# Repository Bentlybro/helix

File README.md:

# Helix

A modular behind-the-ear wearable platform. The ear clip is the mount — snap any module onto it magnetically.

## Concept

Helix is not a single-purpose device. It's a **platform**.

The ear clip attaches to your ear and stays there. Different electronic modules magnetically connect to it — each with their own MCU, sensors, and purpose. Swap modules, change what the device does. The clip is the constant, the module is the variable.

Current modules:
- **Helix IMU** — head pose tracking (roll, pitch, yaw) over BLE
- **Helix Mic** — microphone audio streaming over BLE for speech-to-text

Planned modules: anything that fits behind an ear.

## Hardware

### Ear Clip
3D printed, behind-the-ear hook design with magnetic mounting face. Sits discreetly over the ear like a hearing aid. Houses no electronics — purely mechanical.

### Helix IMU Module
- **MCU**: Seeed XIAO nRF52840 Sense
- **IMU**: Onboard LSM6DS3 (accel + gyro) — 6DOF, 200Hz
- **Connectivity**: BLE 5.0
- **Power**: LP502030 250mAh LiPo + slide switch
- **Extras**: Battery % monitoring, onboard temperature sensor

### Helix Mic Module
- **MCU**: Seeed XIAO nRF52840 Sense
- **Mic**: Onboard PDM microphone — 16kHz 16-bit mono
- **Connectivity**: BLE 5.0
- **Firmware**: Zephyr RTOS

## Repository Structure

```
helix/
├── firmware/
│   ├── helix-imu/          # Arduino (Seeed nRF52 Boards)
│   │   └── helix-imu.ino
│   └── helix-mic/          # Zephyr RTOS (nRF Connect SDK v2.5.0)
│       ├── CMakeLists.txt
│       ├── prj.conf
│       ├── boards/
│       └── src/
├── apps/
│   ├── helix-imu/              # Python BLE receiver (testing)
│   │   ├── receiver.py
│   │   └── scan.py
│   ├── helix-imu-android/      # Android app — live orientation + visualiser
│   └── helix-mic-android/      # Android app — audio stream + Whisper STT
└── hardware/                   # 3D models (coming soon)
```

## BLE Protocol

All Helix modules share a common service UUID with module-specific characteristics.

**Service UUID:** `917649A0-D98E-11E5-9EEC-0002A5D5C51B`

| Characteristic | UUID | Module | Format |
|---|---|---|---|
| Orientation | `917649A1-...` | IMU | 3x float32 (roll, pitch, yaw °) |
| Battery | `917649A2-...` | IMU, Mic | uint8 (0–100%) |
| Temperature | `917649A3-...` | IMU | float32 (°C) |
| Audio | `917649B0-...` | Mic | [seq:2][flags:1][pcm data] |

## Getting Started

### Helix IMU

**Flash firmware (Arduino):**
1. Install Arduino IDE
2. Add board URL: `https://files.seeedstudio.com/arduino/package_seeeduino_arduino_board_index.json`
3. Install **Seeed nRF52 Boards** (non-mbed variant)
4. Install **Seeed Arduino LSM6DS3** library
5. Select **Seeed XIAO BLE Sense - nRF52840**
6. Open `firmware/helix-imu/helix-imu.ino` and upload

**Android app:**
Open `apps/helix-imu-android/` in Android Studio and run.

Features: live roll/pitch/yaw display, 3D direction visualiser, calibration, battery %, temperature.

### Helix Mic

**Flash firmware (Zephyr):**
1. Build with nRF Connect SDK v2.5.0
2. Double-tap reset on XIAO to enter bootloader
3. Drag `zephyr.uf2` onto the `XIAO-SENSE` drive

**Android app:**
Open `apps/helix-mic-android/` in Android Studio and run.

Features: BLE audio receive, WAV buffering, Whisper API transcription.

## Building Firmware (Server)

nRF Connect SDK is set up on the build server.

```bash
# Helix Mic (Zephyr)
cd ~/nrf-sdk/zephyr
west build -b xiao_ble ~/clawd/repos/helix/firmware/helix-mic

# Output
build/zephyr/zephyr.uf2
```

## Status

| Module | Firmware | Android App | Hardware |
|---|---|---|---|
| Helix IMU | ✅ Working | ✅ Working | 🚧 Enclosure in progress |
| Helix Mic | ✅ Advertising | 🚧 In progress | ⬜ Not started |

## License

MIT

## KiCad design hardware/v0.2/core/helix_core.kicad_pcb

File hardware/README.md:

# Helix hardware

Helix as a product: a small computer worn behind the ear, and modules that snap onto it.
The boards here are designed as code with [Via](https://github.com/ThyFriendlyFox/via): each board is
a `design.py`, and the KiCad files, the gerbers and the pictures are generated from it.

## Current version: v0.2

Helix is 2 pieces: a plain printed **hook**, and one **pod** that holds everything and snaps onto
the hook's spine with 3 magnets (6 x 2 mm, 10.4 mm apart). Hooks come in sizes; the pod stays the
same. A different kind of Helix is a different pod on the same hook.

[`v0.2/core`](v0.2/core/design.py) is the pod's board, 13 x 46 mm. Against v0.1 it adds a USB-C socket
to charge and flash, a side-push button on the pod's rear edge, and 2 pads for a wireless charging
receiver; v0.1's module port and its Health board are dropped, and no health sensor is fitted (hair
lies between the pod and the skin). The cell is an LP401230 with its protection circuit, 100 mAh,
over the whole top face. The board is held to PCBWay's published limits. Its gates: ERC, DRC, SIM
and EXPORT pass, GREEN with 2 warnings (the socket's outline drawing runs over the board's edge).
Nobody has built it. [`v0.2/order`](v0.2/order/make_order.py) writes the 3 files PCBWay's order
form takes; its part numbers have not been checked against stock.

Everything below this section describes v0.1 and is kept as its record.

## The product (v0.1)

| Piece | What it is | Electronics |
|---|---|---|
| **Clip** | The hook over the ear. Printed or moulded, in sizes. Magnets hold the Core to it. | None |
| **Core** | The body behind the ear: radio, motion, microphone, cell, charger, one button, one light. Useful on its own. | [`v0.1/core`](v0.1/core/design.py) |
| **Module** | A small board that snaps onto the Core's Helix Port and adds a sense or an output. | [`v0.1/health`](v0.1/health/design.py) is the first |
| **Dock** | Where the Core sits to charge. It meets the same port, so it can also flash firmware over USB. | Not designed yet |

The first prototypes were a Seeed XIAO nRF52840 Sense and a 250 mAh cell in a printed box of
27 x 40 x 13 mm (`3D models/`). The Core's board is 13 x 38 mm. With a cell of about 100 mAh on top and
1 mm of shell, the body comes to about 15 x 40 x 9 mm: half the width and a third of the volume.

## The Helix Port

10 contacts on a 2 x 5 grid, 2.54 mm apart. The Core carries flat gold pads on its back face; a
module or the dock carries spring pins. 2 magnets in each shell, poles opposed, hold the pair and
let it seat only one way round. Seen from above the Core's top face:

| 1 VCHG | 3 GND | 5 USB D+ | 7 USB D- | 9 INT |
|---|---|---|---|---|
| **2 3V0** | **4 GND** | **6 SDA** | **8 SCL** | **10 VMOD** |

| Contact | Direction | What |
|---|---|---|
| VCHG | in | 5 V from a dock. Charges the cell and wakes USB. |
| 3V0 | out | The Core's 3.0 V rail: a module's logic reference. |
| VMOD | out | The cell, 3.0 to 4.2 V, through a load switch. Off until the firmware turns it on; soft start, so snapping a module on does not dip the cell. |
| SDA, SCL | both | I2C at 400 kHz, pulled up to 3V0 on the Core. A module adds 25 pF at most. |
| INT | in | Open drain, active low, pulled up on the Core. A module asks for attention. |
| USB D+, D- | both | The nRF52840's own USB, for the dock. |

A module is found by its I2C addresses. v0.2 should add a small ID EEPROM to every module so the
Core can name what is attached without guessing.

## Core v0.1

| | |
|---|---|
|  |  |

13 x 38 mm, 4 layers, 0.8 mm, matte black, parts on both faces.

| Block | Part | Why |
|---|---|---|
| Radio and processor | Raytac MDBT50Q-1MV2 (nRF52840, chip antenna) | The chip the XIAO carries, so the Zephyr and Arduino firmware carries over. A certified module: no antenna to design. |
| Motion | ST LSM6DS3TR-C at 0x6A | The XIAO Sense's IMU, on the same address. |
| Microphone | Knowles SPH0641LU4H-1, PDM | On the back face; its sound port is a hole through the board. |
| Charger | Microchip MCP73831, 50 mA | Half-hour rate for a 100 mAh cell. STAT goes to the processor. |
| Rail | TI TLV75530, 3.0 V | Holds regulation until the cell is nearly empty. |
| Module power | TI TPS22917 load switch | VMOD on request, slew-limited, discharged when off. |
| Protection | 3 x TI TPD1E05U06 | A TVS diode on each line the dock drives. |
| Cell voltage | 1M / 1M divider into AIN2 | 2 uA. |
| Wearer | Omron B3U button, a white light | One of each. |
| Debug | 3 pads: SWDIO, SWDCLK, nRESET | With 3V0 and GND from the port. |

Firmware pin map (nRF52840):

| Signal | Pin | Signal | Pin |
|---|---|---|---|
| SDA | P0.26 | SCL | P0.27 |
| PDM clock | P0.06 | PDM data | P0.08 |
| IMU INT1 | P0.05 | Module INT | P0.07 |
| Cell voltage / 2 | P0.04 (AIN2) | Module power enable | P1.08 |
| Charger STAT | P1.09 | Button | P0.11 |
| Light (low is on) | P0.12 | nRESET | P0.18 |

## Health v0.1

| | |
|---|---|
|  |  |

13 x 16 mm, 4 layers, 0.8 mm. Spring pins and a 1.8 V regulator on the face that meets the Core; on
the face against the skin, a MAX30102 (pulse and blood oxygen, 0x57) and a TMP117 (skin
temperature, 0x48). It runs only from VMOD, so it draws nothing until the firmware turns it on.

## Where each board stands

| Board | ERC | DRC | SIM | EXPORT | Verdict |
|---|---|---|---|---|---|
| Core | pass | pass | pass: the I2C rise time, 60 corner runs | pass | GREEN with `--strict` |
| Health | pass | pass | no deck | pass | GREEN with `--strict` |

GREEN means the open tools found no fault in the files. It does not mean a built board works.
Nobody has built either board. Before an order:

- **Parts' ratings are not judged.** Neither board has a `ratings.json`: no pin's voltage, no
  capacitor's derating and no regulator's dissipation has been held to its datasheet by a gate.
- **The antenna is not simulated.** The strip under it is bare on all 4 layers as Raytac asks, but
  the cell lies 0.5 mm from its end and a head is beside it. Range has to be measured.
- **The MAX30102's LED supply** is VMOD, and its datasheet asks 3.1 V at the least: the last part
  of the cell's discharge reads no pulse.
- **The microphone's acoustics** (the hole, the shell's port, a mesh against sweat) are not designed.
- **No cell protection on the board.** The cell must carry its own protection circuit.
- **The I2C bus capacitance** in the deck, 50 pF, is an estimate.
- **The spring pin** is named (Mill-Max 0906 series) and its land is drawn, but its outline has not
  been checked against the drawing, and the stack with the Health module on is about 14 mm thick
  at the port. A lower contact would thin it.
- **Skin contact, sweat and charging while worn** are product-safety questions no gate here asks.

## What comes next

1. The shell and the clip for these boards, sized from the assembly: where the magnets, the button
   cap, the light pipe and the microphone's port go.
2. `ratings.json` for both boards, and the charger and regulator as Via's blocks.
3. The dock: 5 V in on USB-C, 10 spring pins, USB through to the Core.
4. Firmware: one image for the Core with the IMU and microphone services, the new pin map, and
   module detection.
5. v0.2 of the Core: a 32.768 kHz crystal for lower idle current, a module ID EEPROM convention,
   and whatever the first built boards teach.

## Working on the boards

Via runs from its Docker image; nothing else is installed. From `hardware/v0.1`, in Git Bash:

```sh
via() { MSYS_NO_PATHCONV=1 docker run --rm -e KICAD10_3DMODEL_DIR=/bodies \
  -v "$PWD/../.3dmodels:/bodies" -v "$PWD:/work" ghcr.io/thyfriendlyfox/via:main "$@"; }

via python3 footprints/make_footprints.py       # the Helix Port's 2 footprints
via python3 models/make_models.py               # bodies for the parts KiCad draws without one
via workcenter design core/design.py --route    # the Core's KiCad project, routed (about 8 minutes)
via workcenter gates core --strict              # ERC, DRC, simulation, export; GREEN means done
via workcenter pictures .                       # every render into docs/
```

`.3dmodels/` holds the part bodies of KiCad's 3D library that the renders need; it is not in the
repository. The `.kicad_*` files open in KiCad 10 to look at; change `design.py`, never them.
Fabrication files are in `<board>/build/fab/` after the gates.

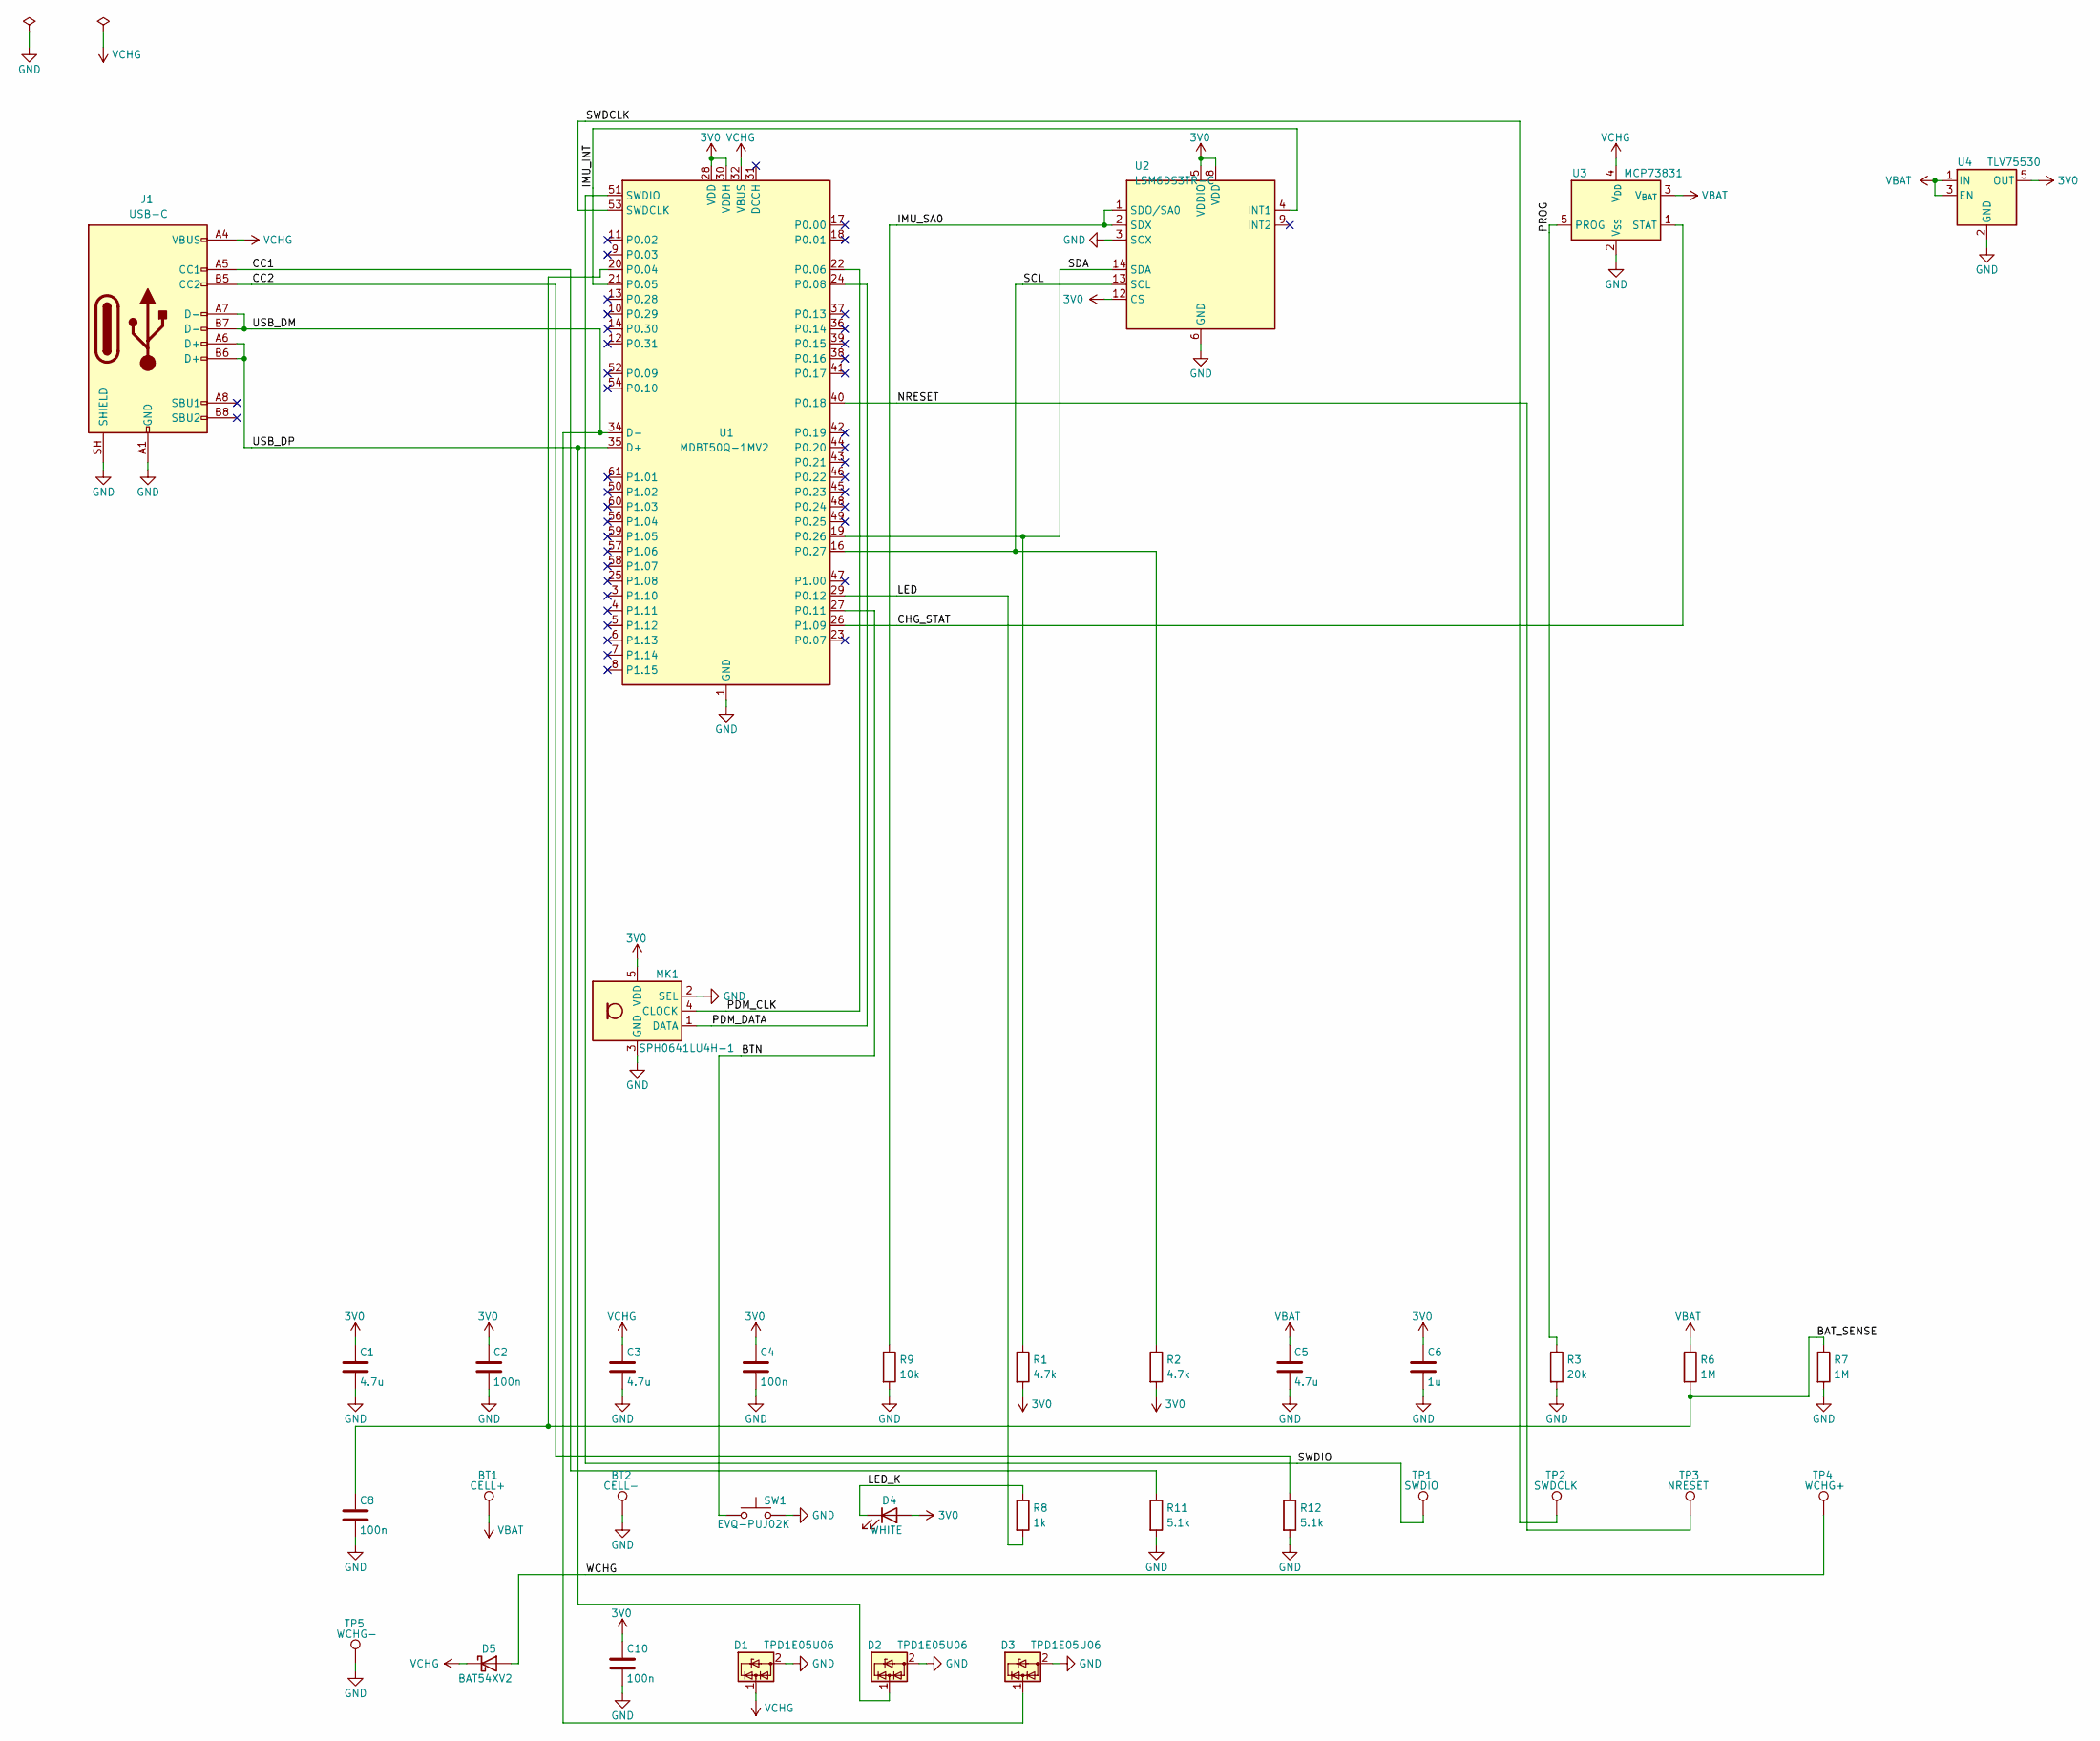
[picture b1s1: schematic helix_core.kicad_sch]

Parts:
BT1: CELL+; TestPoint_Pad_1.5x1.5mm
BT2: CELL-; TestPoint_Pad_1.5x1.5mm
C1, C3, C5: 4.7u; C_0402_1005Metric
C2, C4, C8, C10: 100n; C_0402_1005Metric
C6: 1u; C_0402_1005Metric
D1, D2, D3: TPD1E05U06; D_SOD-523
D4: WHITE; LED_0402_1005Metric
D5: BAT54XV2; D_SOD-523
J1: USB-C; USB_C_Receptacle_HRO_TYPE-C-31-M-12
MK1: SPH0641LU4H-1; Knowles_LGA-5_3.5x2.65mm
R1, R2: 4.7k; R_0402_1005Metric
R3: 20k; R_0402_1005Metric
R6, R7: 1M; R_0402_1005Metric
R8: 1k; R_0402_1005Metric
R9: 10k; R_0402_1005Metric
R11, R12: 5.1k; R_0402_1005Metric
SW1: EVQ-PUJ02K; Panasonic_EVQPUJ_EVQPUA
TP1: SWDIO; TestPoint_Pad_D1.0mm
TP2: SWDCLK; TestPoint_Pad_D1.0mm
TP3: NRESET; TestPoint_Pad_D1.0mm
TP4: WCHG+; TestPoint_Pad_D1.5mm
TP5: WCHG-; TestPoint_Pad_D1.5mm
U1: MDBT50Q-1MV2; Raytac_MDBT50Q
U2: LSM6DS3TR-C; LGA-14_3x2.5mm_P0.5mm_LayoutBorder3x4y
U3: MCP73831; SOT-23-5
U4: TLV75530; SOT-23-5

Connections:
3V0: C1.1, C2.1, C4.1, C6.1, C10.1, D4.2 (A), MK1.5 (VDD), R1.2, R2.2, U1.28 (VDD), U1.30 (VDDH), U2.5 (VDDIO), U2.8 (VDD), U2.12 (CS), U4.5 (OUT)
/BAT_SENSE: C8.1, R6.2, R7.1, U1.20 (P0.04)
/BTN: SW1.1, U1.27 (P0.11)
/CC1: J1.A5 (CC1), R11.1
/CC2: J1.B5 (CC2), R12.1
/CHG_STAT: U1.26 (P1.09), U3.1 (STAT)
/IMU_INT: U1.21 (P0.05), U2.4 (INT1)
/IMU_SA0: R9.1, U2.1 (SDO/SA0), U2.2 (SDX)
/LED: R8.2, U1.29 (P0.12)
/LED_K: D4.1 (K), R8.1
/NRESET: TP3.1, U1.40 (P0.18)
/PDM_CLK: MK1.4 (CLOCK), U1.22 (P0.06)
/PDM_DATA: MK1.1 (DATA), U1.24 (P0.08)
/PROG: R3.1, U3.5 (PROG)
/SCL: R2.1, U1.16 (P0.27), U2.13 (SCL)
/SDA: R1.1, U1.19 (P0.26), U2.14 (SDA)
/SWDCLK: TP2.1, U1.53 (SWDCLK)
/SWDIO: TP1.1, U1.51 (SWDIO)
/USB_DM: D3.1 (I/O), J1.A7 (D-), J1.B7 (D-), U1.34 (D-)
/USB_DP: D2.1 (I/O), J1.A6 (D+), J1.B6 (D+), U1.35 (D+)
/WCHG: D5.2 (A), TP4.1
GND: BT2.1, C1.2, C2.2, C3.2, C4.2, C5.2, C6.2, C8.2, C10.2, D1.2 (GND), D2.2 (GND), D3.2 (GND), J1.A1 (GND), J1.A12 (GND), J1.B1 (GND), J1.B12 (GND), J1.SH (SHIELD), MK1.2 (SEL), MK1.3 (GND), R3.2, R7.2, R9.2, R11.2, R12.2, SW1.2, TP5.1, U1.1 (GND), U1.2 (GND), U1.15 (GND), U1.33 (GND), U1.55 (GND), U2.3 (SCX), U2.6 (GND), U2.7 (GND), U3.2 (V_{SS}), U4.2 (GND)
VBAT: BT1.1, C5.1, R6.1, U3.3 (V_{BAT}), U4.1 (IN), U4.3 (EN)
VCHG: C3.1, D1.1 (I/O), D5.1 (K), J1.A4 (VBUS), J1.A9 (VBUS), J1.B4 (VBUS), J1.B9 (VBUS), U1.32 (VBUS), U3.4 (V_{DD})

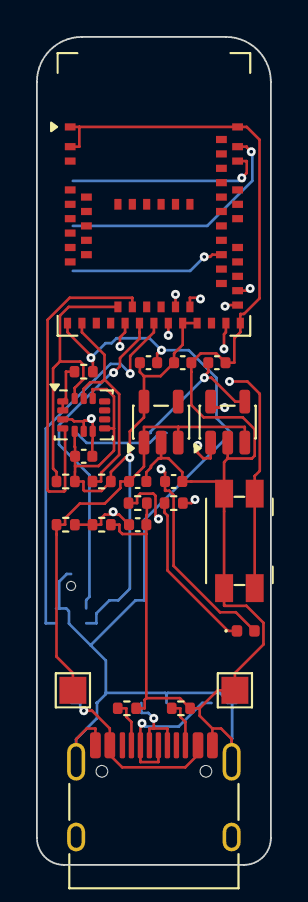
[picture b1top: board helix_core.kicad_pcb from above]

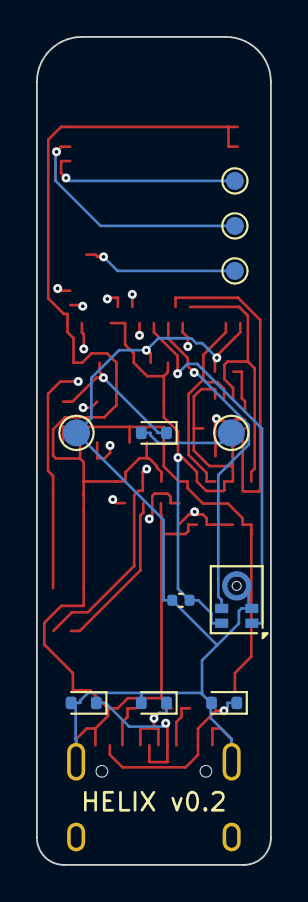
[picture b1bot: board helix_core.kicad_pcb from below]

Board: 4 copper layers, 13.0 x 46.0 mm, 36 parts (11 on the bottom side), 24 nets.

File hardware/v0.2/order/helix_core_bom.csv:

Item,Designator,Qty,Manufacturer,Mfg Part #,Description,Package,Type
1,"C1,C3,C5",3,Murata,GRM155R60J475ME47D,Capacitor 4.7 uF 6.3 V X5R 0402,C_0402_1005Metric,SMD
2,"C2,C4,C8,C10",4,Murata,GRM155R71C104KA88D,Capacitor 100 nF 16 V X7R 0402,C_0402_1005Metric,SMD
3,C6,1,Murata,GRM155R61A105KE15D,Capacitor 1 uF 10 V X5R 0402,C_0402_1005Metric,SMD
4,"D1,D2,D3",3,Texas Instruments,TPD1E05U06DYAR,"TVS diode 5.5 V 0.45 pF, SOD-523",D_SOD-523,SMD
5,D4,1,any,"white LED, 0402, 5 mA",Status light: PCBWay to propose a stocked part,LED_0402_1005Metric,SMD
6,D5,1,onsemi,BAT54XV2T1G,"Schottky diode 30 V 200 mA, SOD-523",D_SOD-523,SMD
7,J1,1,HRO (Korean Hroparts Elec),TYPE-C-31-M-12,"USB Type-C receptacle, 16 pin",USB_C_Receptacle_HRO_TYPE-C-31-M-12,Thru-hole + SMD
8,MK1,1,Knowles,SPH0641LU4H-1,"PDM MEMS microphone, bottom port",Knowles_LGA-5_3.5x2.65mm,SMD
9,"R1,R2",2,Yageo,RC0402FR-074K7L,Resistor 4.7 k 1 % 0402,R_0402_1005Metric,SMD
10,"R11,R12",2,Yageo,RC0402FR-075K1L,Resistor 5.1 k 1 % 0402,R_0402_1005Metric,SMD
11,R3,1,Yageo,RC0402FR-0720KL,Resistor 20 k 1 % 0402,R_0402_1005Metric,SMD
12,"R6,R7",2,Yageo,RC0402FR-071ML,Resistor 1 M 1 % 0402,R_0402_1005Metric,SMD
13,R8,1,Yageo,RC0402FR-071KL,Resistor 1 k 1 % 0402,R_0402_1005Metric,SMD
14,R9,1,Yageo,RC0402FR-0710KL,Resistor 10 k 1 % 0402,R_0402_1005Metric,SMD
15,SW1,1,Panasonic,EVQ-PUJ02K,Side-push tactile switch 4.7 x 3.5 x 1.65 mm,Panasonic_EVQPUJ_EVQPUA,SMD
16,U1,1,Raytac,MDBT50Q-1MV2,"nRF52840 Bluetooth module, chip antenna",Raytac_MDBT50Q,SMD
17,U2,1,STMicroelectronics,LSM6DS3TR-C,"6-axis IMU, LGA-14",LGA-14_3x2.5mm_P0.5mm_LayoutBorder3x4y,SMD
18,U3,1,Microchip,MCP73831T-2ACI/OT,"Li-ion charger 4.2 V, SOT-23-5",SOT-23-5,SMD
19,U4,1,Texas Instruments,TLV75530PDBVR,"Regulator 3.0 V 500 mA, SOT-23-5",SOT-23-5,SMD

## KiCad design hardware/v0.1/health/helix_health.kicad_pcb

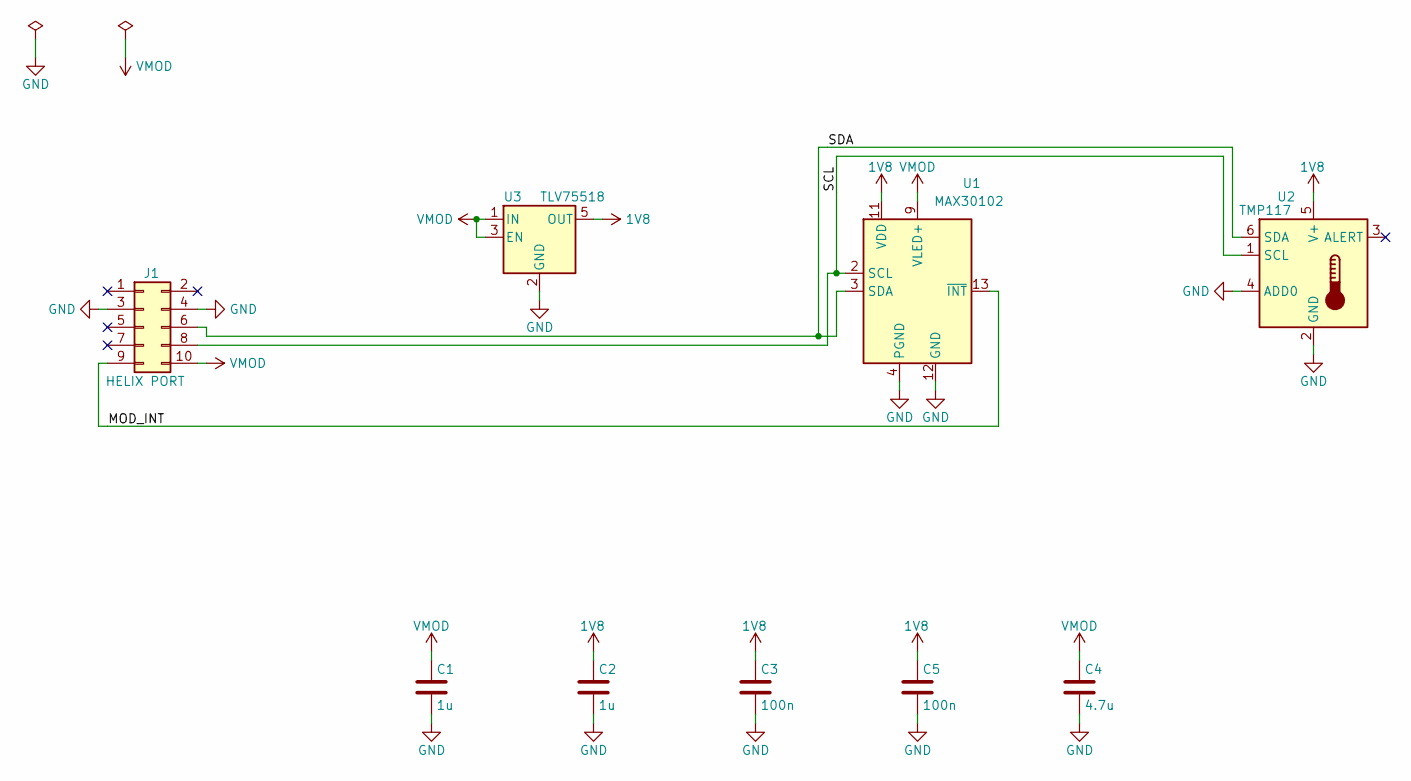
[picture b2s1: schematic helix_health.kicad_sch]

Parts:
C1, C2: 1u; C_0402_1005Metric
C3, C5: 100n; C_0402_1005Metric
C4: 4.7u; C_0402_1005Metric
J1: HELIX PORT; HelixPort_Module_2x05_P2.54mm
U1: MAX30102; Maxim_OLGA-14_3.3x5.6mm_P0.8mm
U2: TMP117; WSON-6-1EP_2x2mm_P0.65mm_EP1x1.6mm
U3: TLV75518; SOT-23-5

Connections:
1V8: C2.1, C3.1, C5.1, U1.11 (VDD), U2.5 (V+), U3.5 (OUT)
/MOD_INT: J1.9, U1.13 (~INT)
/SCL: J1.8, U1.2 (SCL), U2.1 (SCL)
/SDA: J1.6, U1.3 (SDA), U2.6 (SDA)
GND: C1.2, C2.2, C3.2, C4.2, C5.2, J1.3, J1.4, U1.4 (PGND), U1.12 (GND), U2.2 (GND), U2.4 (ADD0), U3.2 (GND)
VMOD: C1.1, C4.1, J1.10, U1.9 (VLED+), U1.10 (VLED+), U3.1 (IN), U3.3 (EN)

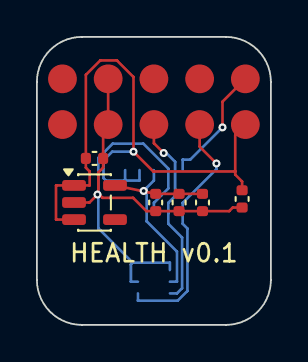
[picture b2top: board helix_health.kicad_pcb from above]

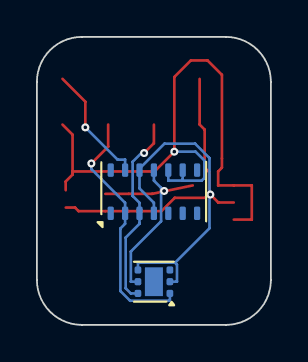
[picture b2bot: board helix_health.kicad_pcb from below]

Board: 4 copper layers, 13.0 x 16.0 mm, 9 parts (2 on the bottom side), 6 nets.

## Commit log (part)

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2026-03-27 Initial idea and planning doc
2026-03-27 Remove Lucid reference — this is its own thing
2026-03-27 Fix firmware for Seeed LSM6DS3 library
    - Use Seeed's LSM6DS3 library (correct for XIAO Sense)
    - Simplify BLE to individual float characteristics
    - Update Python receiver to match
2026-03-27 Fix: use pre-instantiated global IMU object
2026-03-27 Fix: use readAcceleration/readGyroscope API
2026-03-27 Add LED blink status codes + serial wait for debug
2026-03-27 Rewrite BLE using Bluefruit stack (non-mbed board package)
2026-03-27 Fix sensor fusion units: atan2 rad → deg before complementary filter
2026-03-27 Pack orientation into single 12-byte notify, real dt, cleaner receiver
2026-03-27 Move firmware into helix-imu/ folder (Arduino naming requirement)
2026-03-27 Rename receiver-python to helix-imu, add apps README
2026-03-28 Add gradle.properties (useAndroidX, suppressCompileSdk warning)
2026-03-28 Add battery % reading to firmware and Android app
2026-03-28 Add IMU temperature sensor — firmware + Android app
2026-03-28 Fix BLE GATT queue — serialize descriptor writes and reads
2026-03-28 Fix battery: use 3.6V internal ref, remove broken AR_INTERNAL_3_0
2026-03-28 Fix axis: swap pitch/yaw gyro mapping
2026-03-28 Fix axis signs: nod/turn/tilt all positive in correct direction
2026-03-28 Swap forward/up arrows in visualiser
2026-03-28 Fix pitch arrow direction, 200Hz IMU, lower alpha, request high BLE priority
2026-03-28 Swap Forward/Up legend labels in visualiser
2026-03-28 Add navigationBarsPadding so button clears system nav bar
2026-03-28 Add helix-mic Zephyr firmware — PDM mic + BLE audio stream
2026-03-28 Add Helix Mic Android app - BLE audio receiver with Whisper transcription
2026-03-28 Fix transcript card height so connect button is visible
2026-03-28 Fix audio buffer crash — use chunk list instead of ByteArray concat
2026-03-28 fix(helix-mic): buffer size, mic start fallback, PDM device node, connection handling
    - transport.c: increase audio_data buffer from 128 to 700 bytes (20ms PCM at 16kHz = 640 bytes)
    - transport.c: add direct mic start on connect instead of relying on callback
    - main.c: add fallback mic start in main loop if connected but not running
    - main.c: track mic_running state to prevent double starts
    - mic.c: use DT_ALIAS(dmic_dev) with fallback to dmic0/pdm0 node labels
    - xiao_ble.overlay: add dmic-dev alias for broader compatibility
2026-03-28 feat(helix-mic): add USB CDC-ACM serial logging for debug output
    - Enable USB CDC-ACM, UART console, and LOG_BACKEND_UART in prj.conf
    - Call usb_enable() at start of main() with 1s enumeration delay
    - Add detailed error logging around mic start (error code + reason)
    - Add connection/disconnection state logging
    - Firmware now outputs all LOG_INF/WRN/ERR to USB serial at 115200 baud
    View logs: screen /dev/ttyACM0 115200 (Linux/Mac)
2026-03-28 Fix: increase dmic thread stack 1024→4096 bytes (stack overflow crash)
2026-03-28 Fix: write audio CCCD immediately on discover, don't queue it
2026-03-28 Remove USB logging (conflicts with BLE), switch to RTT logging
2026-03-28 helix-mic: fix low packet rate, add playback button, real-time byte counter
    - Remove isRawPcm filter in onCharacteristicChanged — accept all audio data
    - Add totalAudioBytesFlow StateFlow for real-time UI updates
    - Fix audioDurationSec to use totalAudioBytes instead of audioBuffer.size
    - Add Play button for audio playback debugging (AudioTrack)
    - Fix Transcribe button enabled state to use totalAudioBytes
2026-03-28 Fix AudioTrack: use MODE_STREAM with constructor, avoid JNI Builder issue
2026-03-28 Fix Android 16 JNI crash: copy uuid+value before when() in onCharacteristicChanged
2026-03-28 mic: rewrite to nrfx_pdm direct — fix crash after 3 packets
    Replace Zephyr AUDIO_DMIC abstraction with direct nrfx_pdm driver:
    - Double-buffered 1600-sample (100ms) frames via IRQ handler
    - IRQ_DIRECT_CONNECT for proper PDM IRQ routing
    - HFCLK start before PDM init
    - Disable pdm0 Zephyr node in overlay to avoid conflict
    - Simplified callback: raw int16_t* buffer instead of audio_frame struct
2026-03-28 Fix BLE buffer overflow: retry on ENOBUFS, increase TX buf count to 16
2026-03-28 feat(helix-mic): ring buffer + pusher thread audio pipeline
    Replace direct transport_send_audio() calls from PDM callback with:
    - Ring buffer (8 frames / 25.6KB) written from mic ISR context
    - Dedicated pusher thread draining ring buffer into BLE notifications
    at controlled rate with backpressure handling
    Fixes audio quality issue (buzz/noise) caused by flooding BLE stack
    from interrupt context. Based on Omi firmware architecture.
2026-03-28 Fix MTU: Android requests 247 bytes before service discovery
2026-03-28 feat(helix-mic): rewrite to Zephyr DMIC API, drop nrfx_pdm
    - Replace direct nrfx_pdm usage with Zephyr's standard DMIC driver
    - Device tree overlay: regulator-fixed for mic enable (P1.10) with
    regulator-boot-on, pdm0 pinctrl for CLK/DIN, PCLK32M_HFXO clock
    - mic.c: k_mem_slab buffer management, dedicated reader thread that
    calls dmic_read() in a loop and invokes frame callback
    - prj.conf: CONFIG_AUDIO + CONFIG_AUDIO_DMIC, removed CONFIG_NRFX_PDM
2026-03-28 Increase L2CAP TX MTU to 247 for larger BLE audio packets
2026-03-28 Fix PDM pins: CLK=P1.0 DATA=P0.16 (was swapped!)
2026-03-28 Remove fallback mic start, only start on CCCD subscription
2026-03-28 Add pusher debug logging to trace audio send failures
2026-03-28 Fix ANR: ArrayDeque + throttle UI updates to every 50 packets
2026-03-28 Add BLE audio test script - connect, record, save WAV + audio stats
2026-03-28 Pace pusher at 7ms between packets, fix test script disconnect handling
2026-03-28 Fix test script: check is_connected before stop_notify
2026-03-28 Back to PDM_CHAN_LEFT, force P1.10 HIGH manually in mic_start
2026-03-28 feat(helix-mic): realtime transcription via OpenAI WebSocket API
    - Replace 5s chunked Whisper with OpenAI Realtime Transcription API (WebSocket)
    - Stream BLE audio with 16kHz→24kHz resampling (linear interpolation)
    - Live partial text display (italic/gray) during speech
    - Completed segments with timestamps shown as solid text
    - Add Sessions screen to browse past saved sessions
    - Add Session Detail screen with transcript + summary
2026-03-28 Remove emojis from UI, use text labels instead
2026-03-28 Fix battery ADC: configure SAADC AIN7, enable P0.14 divider, bigger ring buf
2026-03-28 helix-mic: transcription-verified enrollment flow + server enrollment check
    - Replace countdown timer enrollment with transcription-based verification
    - Each phrase is verified via fuzzy match (60% word overlap) against live
    transcription from the local server WebSocket
    - Live 'Heard: ...' feedback shows what the transcriber is picking up
    - Auto-advance with checkmark animation when phrase matches
    - 15s timeout per phrase with 'Try Again' button
2026-03-28 Fix speakers API parsing: response is {speakers:[]} not raw array
2026-03-29 helix-mic: redesign UI — monochrome technical illustration aesthetic
    - Replace cyan/teal accent palette with monochrome (white, grays, near-black)
    - Recording-only accent: muted red #CC3333
    - Background: #0A0A0A, all cards/surfaces removed or made barely visible
    - 0.5dp hairline dividers instead of thick borders
    - Sharp corners (0dp), no rounded pills or Material Design feel
    - Typography: monospace, light weight, wide letter-spacing, uppercase headers
2026-03-29 Fix foreground service: start on BLE connect, wake lock, state updates
2026-04-16 fix firmware: battery ADC, BLE connection, MTU negotiation for NCS v3.2.4
    Battery ADC was returning 0xFF (unknown) due to wrong SAADC input constant —
    SAADC_CH_PSELP_PSELP_AnalogInput7 (0x08) is the raw register value, but
    nrfx on NCS v3.2.4 expects the generic index NRF_SAADC_AIN7 (7). Also fixed
    ADC gain (1/6), acquisition time (40us for high-Z divider), GPIO polarity
    (P0.14 active-low), and voltage divider ratio (1547/510 per actual resistors).
    BLE connection was deadlocking because firmware and Android both initiated MTU
2026-04-16 upgrade whisper.cpp v1.7.2 → v1.8.4, optimize on-device transcription
    Upgraded whisper.cpp for better CPU inference performance and NEON
    optimizations. Tuned transcription pipeline: 6 threads (was 4),
    300ms silence timeout (was 500ms), 10s max chunks (was 20s) for
    snappier end-of-speech detection and shorter inference waits.
    Vulkan GPU build infrastructure added (pre-generated shaders, Vulkan
    headers) but GPU disabled at runtime — Adreno driver crashes on ggml
2026-04-16 add transcription stats: backend label, per-segment timing, session stats tab
    Show active backend (DEVICE/OPENAI/LOCAL) in the status line next to
    battery. Each transcript line now shows inference time right-aligned.
    Session detail view has TRANSCRIPT/STATS tabs — stats show segments,
    words, WPM, avg/min/max inference time, and real-time factor.
    All three backends instrumented: WhisperCpp tracks inference elapsed,
    OpenAI tracks first-delta-to-completed latency, LocalServer tracks
2026-04-16 add quantized whisper models (Q5_1) — same accuracy, 58% smaller
    BASE.EN Q5 (60 MB) is now the default, replacing BASE.EN F16 (142 MB).
    Zero WER difference per arxiv 2503.09905. Also added SMALL.EN Q5
    (190 MB) which is more accurate than base while being smaller than
    the old F16 base model.
    Full precision F16 models remain as options for comparison.
2026-04-16 add apps/helix-mic-android/app/src/main/java/com/helix/mic/WebhookClient.kt apps/helix-mic-android/app/src/main/java/com/helix/mic/MainActivity.kt
    add webhook integration pipeline for live segments and session summaries
    New INTEGRATIONS section in settings with configurable webhook URL
    and toggles for live segment posting and session summary posting.
    WebhookClient POSTs JSON payloads to the endpoint — fire-and-forget
    on IO dispatcher, failures logged but never crash the app.
    Both toggles off by default. Enables feeding transcripts to external
2026-04-16 remove dead code: unused codec module, WhisperClient.kt, gain define
    codec.c/h was stubbed for Opus encoding but never implemented — audio
    goes raw PCM from ring buffer to BLE. WhisperClient.kt (REST Whisper-1
    API) was superseded by WhisperCppClient (on-device JNI). SOFTWARE_GAIN_SHIFT
    in mic.c was unused (gain applied Android-side).
2026-04-16 add session export: share TXT transcript, SRT subtitles, and WAV audio
    EXPORT button on session detail shares via Android share sheet. Generates
    plain text transcript with timestamps, SRT subtitle file with proper
    timecodes, and includes the WAV audio recording if available.
    FileProvider configured for cache/exports and session-audio directories.
2026-04-16 fix export/delete buttons hidden behind navigation bar
